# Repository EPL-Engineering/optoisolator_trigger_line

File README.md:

# Optoisolator Trigger Line Circuit

### Description
The optoisolator circuit in its current state only supports two channels. A PCB has been designed to support 8 optocoupled digital IO channels. The parts have been ordered and the board just needs to be assembled and installed.

### TODO
- Solder components to PCB
- Create custom cables with sub-D connectors on both ends
- Validate functionality and install

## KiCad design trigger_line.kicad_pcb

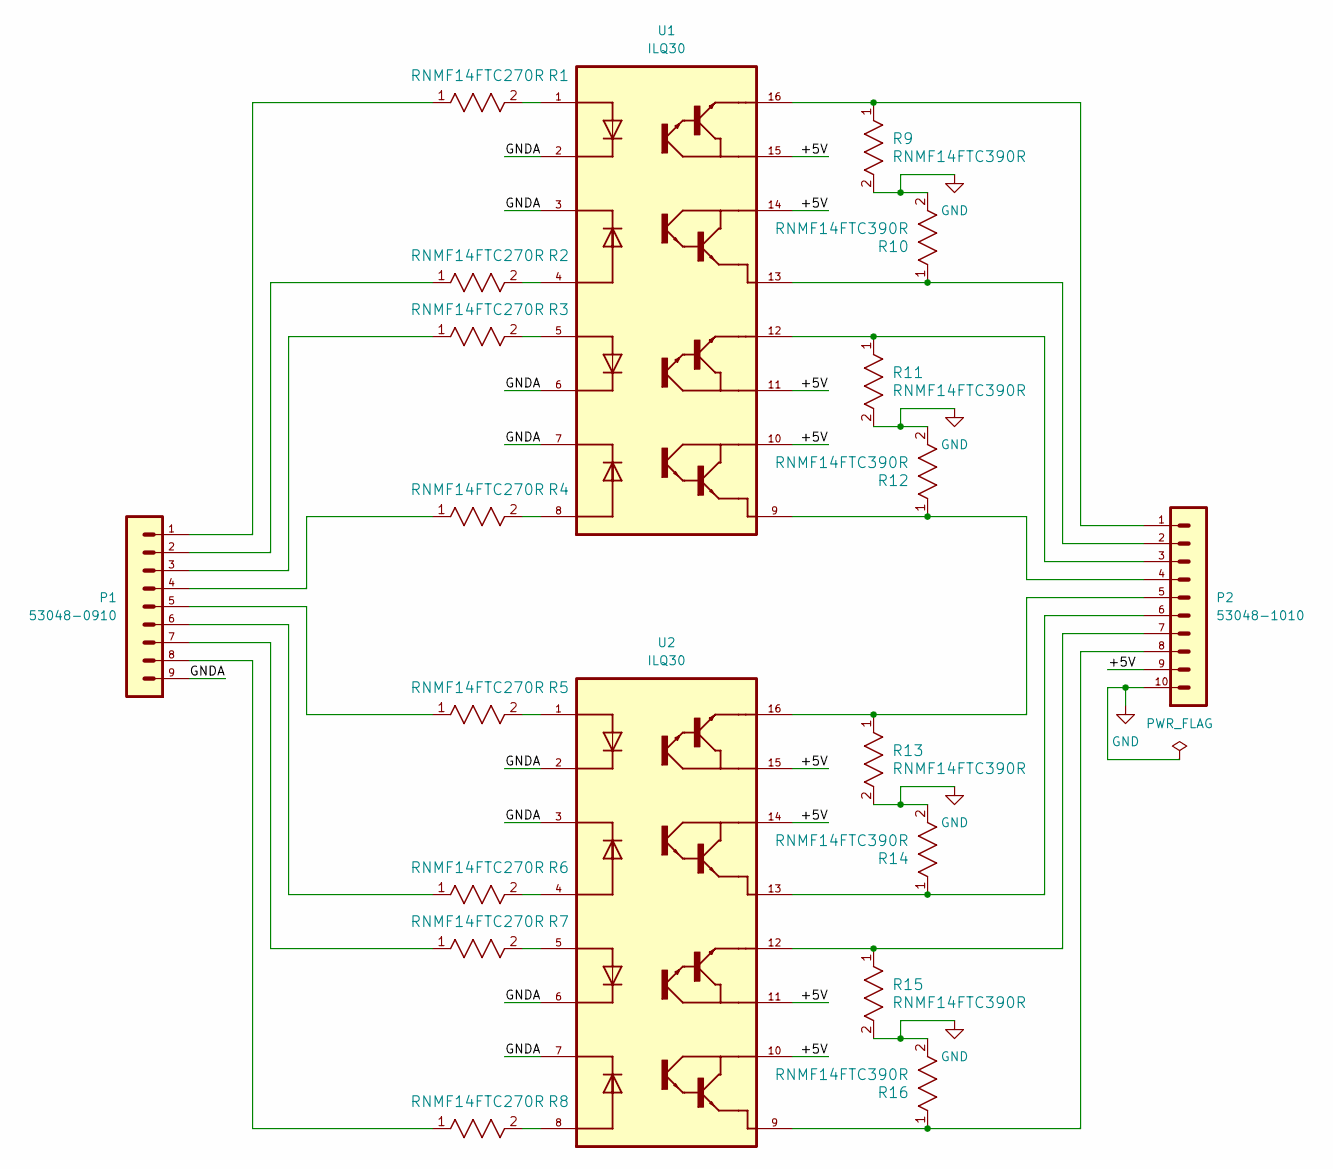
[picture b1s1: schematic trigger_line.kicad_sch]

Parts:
P1: 53048-0910; DigiKey_Part_Number WM1749-ND
P2: 53048-1010; DigiKey_Part_Number WM1750-ND
R1, R2, R3, R4, R5, R6, R7, R8: RNMF14FTC270R; STA_RNMF14_STP
R9, R10, R11, R12, R13, R14, R15, R16: RNMF14FTC390R; STA_RNMF14_STP
U1, U2: ILQ30; DIP762W51P254L1992H425Q16

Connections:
/+5V: P2.9, U1.10, U1.11, U1.14, U1.15, U2.10, U2.11, U2.14, U2.15
/GNDA: P1.9, U1.2, U1.3, U1.6, U1.7, U2.2, U2.3, U2.6, U2.7
GND: P2.10, R9.2, R10.2, R11.2, R12.2, R13.2, R14.2, R15.2, R16.2
unnamed: P1.1, R1.1
unnamed: P1.2, R2.1
unnamed: P1.3, R3.1
unnamed: P1.4, R4.1
unnamed: P1.5, R5.1
unnamed: P1.6, R6.1
unnamed: P1.7, R7.1
unnamed: P1.8, R8.1
unnamed: P2.1, R9.1, U1.16
unnamed: P2.2, R10.1, U1.13
unnamed: P2.3, R11.1, U1.12
unnamed: P2.4, R12.1, U1.9
unnamed: P2.5, R13.1, U2.16
unnamed: P2.6, R14.1, U2.13
unnamed: P2.7, R15.1, U2.12
unnamed: P2.8, R16.1, U2.9
unnamed: R1.2, U1.1
unnamed: R2.2, U1.4
unnamed: R3.2, U1.5
unnamed: R4.2, U1.8
unnamed: R5.2, U2.1
unnamed: R6.2, U2.4
unnamed: R7.2, U2.5
unnamed: R8.2, U2.8

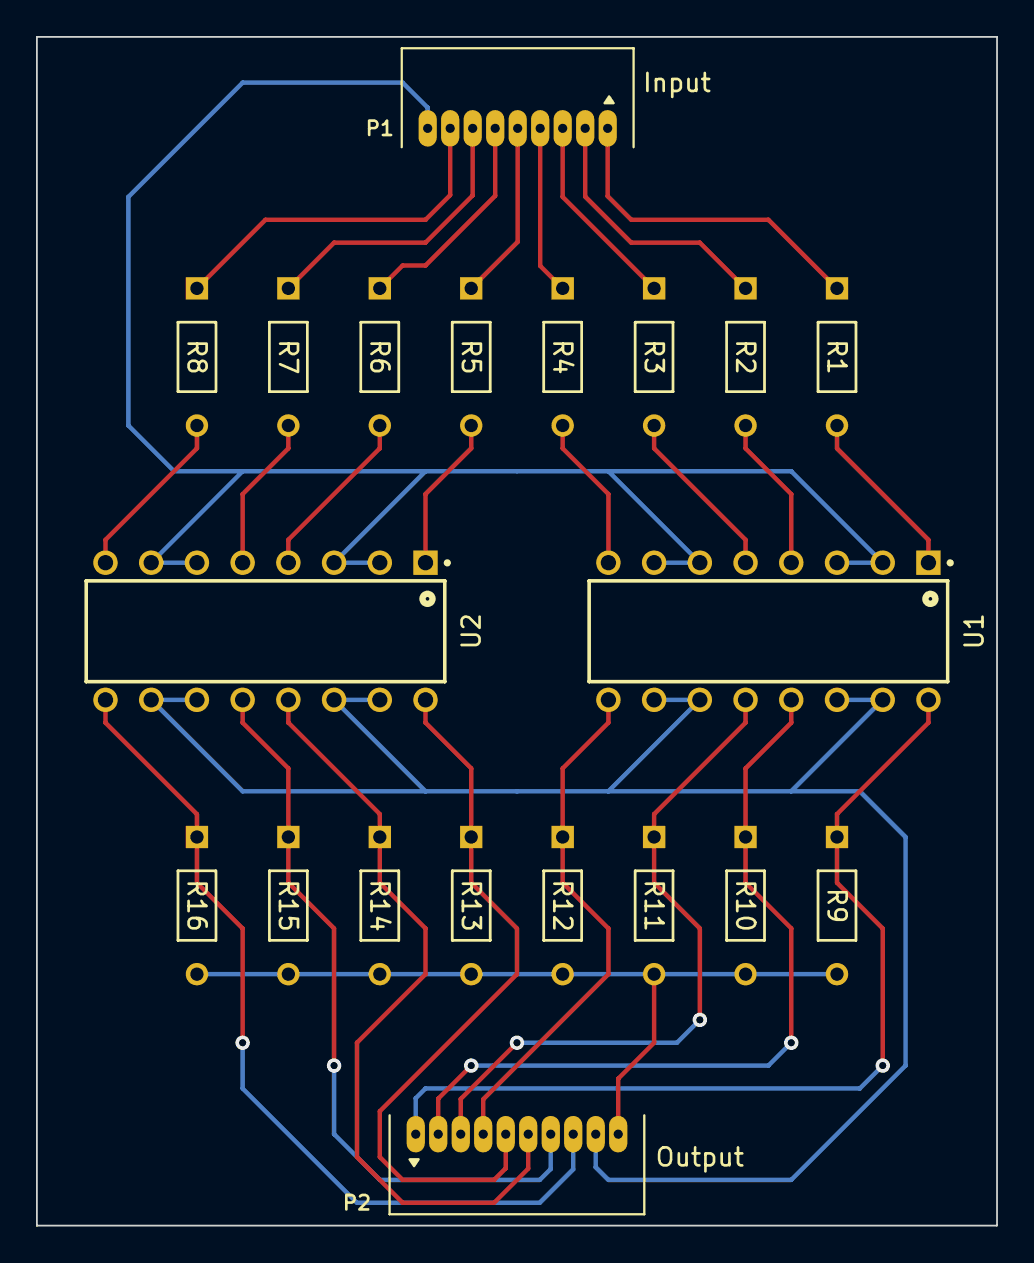
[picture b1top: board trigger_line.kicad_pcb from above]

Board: 2 copper layers, 53.3 x 66.0 mm, 20 parts (0 on the bottom side), 27 nets.

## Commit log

2023-12-28 initial
2023-12-29 schematic
2024-01-08 first order
2024-01-11 added pdf files
2024-04-16 repo organization
